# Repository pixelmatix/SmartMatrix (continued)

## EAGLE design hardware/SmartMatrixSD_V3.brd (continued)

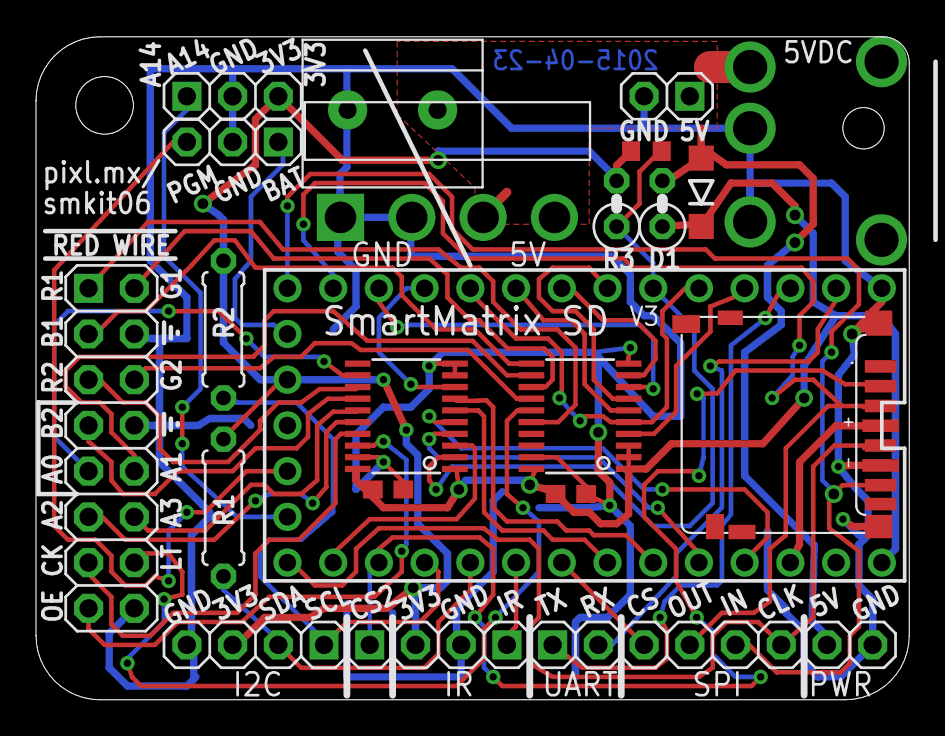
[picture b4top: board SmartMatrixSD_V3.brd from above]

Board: 2 copper layers, 48.5 x 36.8 mm, 25 parts (1 on the bottom side), 43 nets.

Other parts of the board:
U$5: PIXELMATIX-LOGO-235X135

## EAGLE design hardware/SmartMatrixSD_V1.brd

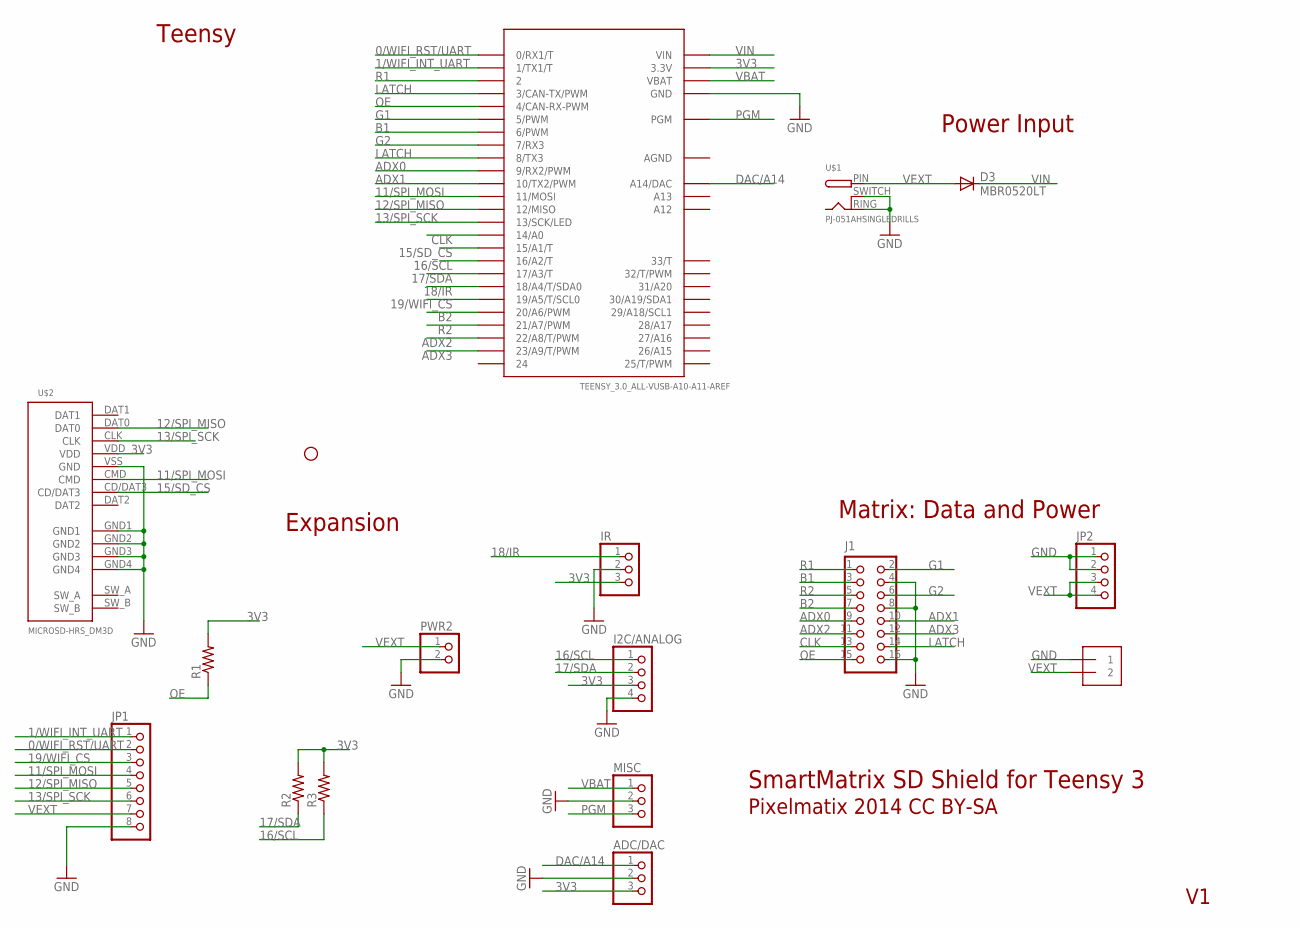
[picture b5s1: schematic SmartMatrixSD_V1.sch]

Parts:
ADC/DAC: PINHD-1X03_2.54-S; 1X03-S
D3: MBR0520LT; SOD123
I2C/ANALOG: PINHD-1X04_2.54-S; 1X04-S
IR: PINHD-1X03_2.54-S; 1X03-S
J1: CON_HEADER_2X08-PTH-SHROUDED; PINSHRD_PTH_2X08
J4: 1X2-5.0; 1X2-5.0MM
JP1: PINHD-1X08_2.54-S; 1X08-S
JP2: PINHD-1X04_1.56; 1X04-1.56"
JP5: STAND-OFFSTAND-OFF-3MM; STAND-OFF-3MM
MISC: PINHD-1X03_2.54-S; 1X03-S
PWR2: PINHD-1X02_2.54-S; 1X02-S
R1: R-US_R0603; R0603
R2, R3: R-US_0207/7; 0207/7
U$1: PJ-051AHSINGLEDRILLS; PJ-051AH-SINGLEDRILLS
U$2: MICROSD-HRS_DM3D; DM3D
U$3: TEENSY_3.0_ALL-VUSB-A10-A11-AREF; TEENSY_3.0_ALLPINS-VUSB-A11-A10-AREF

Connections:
0/WIFI_RST/UART: JP1.2, U$3.0 (0/RX1/T)
1/WIFI_INT_UART: JP1.1, U$3.1 (1/TX1/T)
3V3: ADC/DAC.3, I2C/ANALOG.3, IR.3, R1.2, R2.2, R3.2, U$2.VDD, U$3.3.3V, U$3.3.3V1 (3.3V), U$3.3.3V2 (3.3V)
11/SPI_MOSI: JP1.4, U$2.CMD, U$3.11 (11/MOSI)
12/SPI_MISO: JP1.5, U$2.DAT0, U$3.12 (12/MISO)
13/SPI_SCK: JP1.6, U$2.CLK, U$3.13 (13/SCK/LED)
15/SD_CS: U$2.CD/DAT3, U$3.15/A1 (15/A1/T)
16/SCL: I2C/ANALOG.1, R3.1, U$3.16/A2 (16/A2/T)
17/SDA: I2C/ANALOG.2, R2.1, U$3.17/A3 (17/A3/T)
18/IR: IR.1, U$3.18/A4 (18/A4/T/SDA0)
19/WIFI_CS: JP1.3, U$3.19/A5 (19/A5/T/SCL0)
ADX0: J1.9, U$3.9 (9/RX2/PWM)
ADX1: J1.10, U$3.10 (10/TX2/PWM)
ADX2: J1.11, U$3.22/A8 (22/A8/T/PWM)
ADX3: J1.12, U$3.23/A9 (23/A9/T/PWM)
AGND: U$3.AGND
B1: J1.3, U$3.6 (6/PWM)
B2: J1.7, U$3.20/A6 (20/A6/PWM)
CLK: J1.13, U$3.14/A0
DAC/A14: ADC/DAC.1, U$3.RESET (A14/DAC)
G1: J1.2, U$3.5 (5/PWM)
G2: J1.6, U$3.7 (7/RX3)
GND: ADC/DAC.2, I2C/ANALOG.4, IR.2, J1.4, J1.8, J1.16, J4.1, JP1.8, JP2.1, JP2.2, MISC.2, PWR2.2, U$1.RING (GND), U$1.SWITCH (GNDBREAK), U$2.GND1, U$2.GND2, U$2.GND3, U$2.GND4, U$2.VSS (GND), U$3.GND, U$3.GND1 (GND), U$3.GND2 (GND)
LATCH: J1.14, U$3.3 (3/CAN-TX/PWM), U$3.8 (8/TX3)
OE: J1.15, R1.1, U$3.4 (4/CAN-RX-PWM)
PGM: MISC.3, U$3.PGM
R1: J1.1, U$3.2
R2: J1.5, U$3.21/A7 (21/A7/PWM)
VBAT: MISC.1, U$3.VBAT
VEXT: D3.A, J4.2, JP1.7, JP2.3, JP2.4, PWR2.1, U$1.PIN (PWR)
VIN: D3.C, U$3.VIN

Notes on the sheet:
SmartMatrix SD Shield for Teensy 3
Pixelmatix 2014 CC BY-SA
Teensy
Power Input
Matrix: Data and Power
Expansion

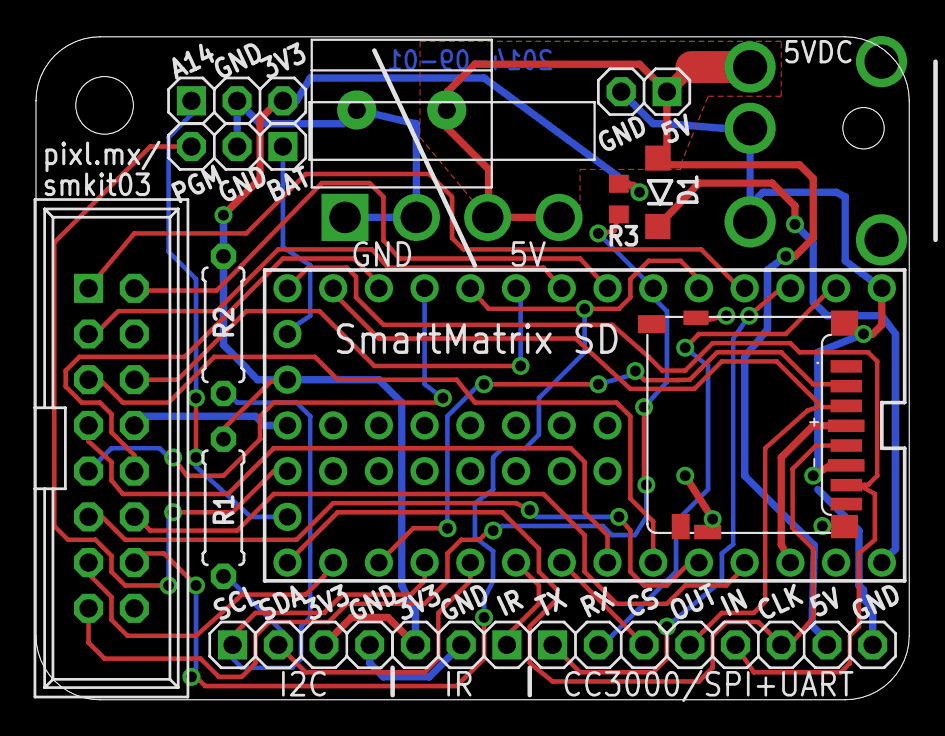
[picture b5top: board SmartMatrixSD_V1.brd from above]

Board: 2 copper layers, 48.5 x 36.8 mm, 17 parts (0 on the bottom side), 30 nets.

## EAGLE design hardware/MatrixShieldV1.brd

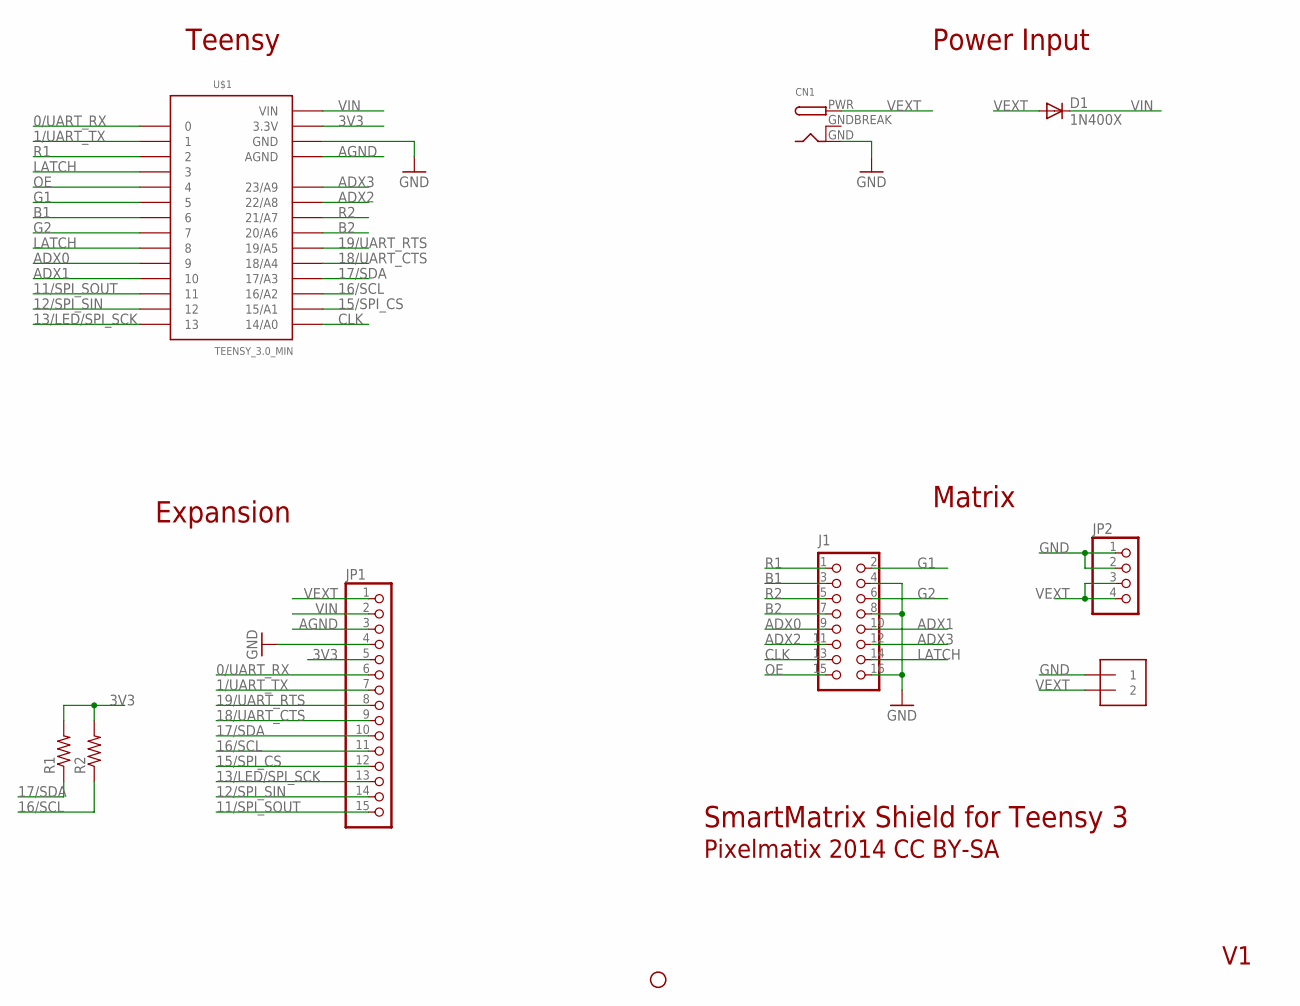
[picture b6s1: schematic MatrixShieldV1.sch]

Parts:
CN1: DCBARRELPTH; DCJACK_2MM_PTH
D1: 1N400X; DIODE-TH-0.3"
J1: CON_HEADER_2X08-PTH-SHROUDED; PINSHRD_PTH_2X08
J4: 1X2-5.0; 1X2-5.0MM
JP1: PINHD-1X15_2.54-S; 1X15-S
JP2: PINHD-1X04_1.56; 1X04-1.56"
JP5: STAND-OFFSTAND-OFF-3MM; STAND-OFF-3MM
R1, R2: R-US_0207/7; 0207/7
U$1: TEENSY_3.0_MIN

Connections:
0/UART_RX: JP1.6, U$1.0
1/UART_TX: JP1.7, U$1.1
3V3: JP1.5, R1.2, R2.2, U$1.3.3V
11/SPI_SOUT: JP1.15, U$1.11
12/SPI_SIN: JP1.14, U$1.12
13/LED/SPI_SCK: JP1.13, U$1.13
15/SPI_CS: JP1.12, U$1.15/A1
16/SCL: JP1.11, R2.1, U$1.16/A2
17/SDA: JP1.10, R1.1, U$1.17/A3
18/UART_CTS: JP1.9, U$1.18/A4
19/UART_RTS: JP1.8, U$1.19/A5
ADX0: J1.9, U$1.9
ADX1: J1.10, U$1.10
ADX2: J1.11, U$1.22/A8
ADX3: J1.12, U$1.23/A9
AGND: JP1.3, U$1.AGND
B1: J1.3, U$1.6
B2: J1.7, U$1.20/A6
CLK: J1.13, U$1.14/A0
G1: J1.2, U$1.5
G2: J1.6, U$1.7
GND: CN1.GND, J1.4, J1.8, J1.16, J4.1, JP1.4, JP2.1, JP2.2, U$1.GND
GNDBREAK: CN1.GNDBREAK
LATCH: J1.14, U$1.3, U$1.8
OE: J1.15, U$1.4
R1: J1.1, U$1.2
R2: J1.5, U$1.21/A7
VEXT: CN1.PWR, D1.A, J4.2, JP1.1, JP2.3, JP2.4
VIN: D1.C, JP1.2, U$1.VIN

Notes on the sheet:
SmartMatrix Shield for Teensy 3
Pixelmatix 2014 CC BY-SA
Teensy
Power Input
Matrix
Expansion

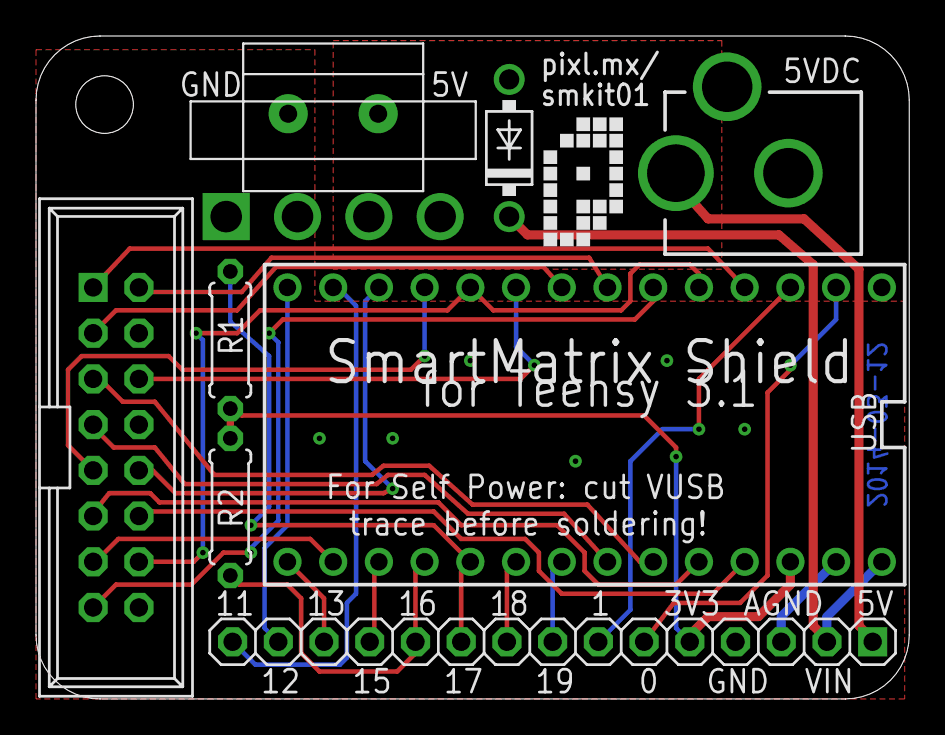
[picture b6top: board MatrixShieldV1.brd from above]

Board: 2 copper layers, 48.5 x 36.8 mm, 11 parts (0 on the bottom side), 28 nets.

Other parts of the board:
U$4: PIXELMATIX-LOGO-300

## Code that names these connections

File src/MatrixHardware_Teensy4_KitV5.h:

// Hardware-specific header file for the SmartLED Shield for Teensy 4 (V5):
//    Only Teensy 4.0/4.1 models are supported.
//
// Some of the pin assignments can be changed using solderable jumpers on the adapter board:
// JP4:
//    Default: Pin 7 connected to BUFFER_CLK, Pin 8 free
//    Alt: Pin 8 connected to BUFFER_CLK, Pin 7 free
//      To use the alternate clock pin, in addition to soldering the jumper you must set flag SMARTMATRIX_OPTIONS_T4_CLK_PIN_ALT in kMatrixOptions
// JP2 & JP3:
//    Default: Pin 4 connected to APA_CLK, Pin 5 connected to APA_DAT (intended for APA102 driving via SPI emulation), LED Matrix is drivable at the same time
//    Alt: Pins 4 & 5 free, Pin 13 connected to APA_CLK, Pin 11 connected to APA_DAT (intended for APA102 driving via hardware SPI), LED Matrix not drivable at the same time

// Note: only one MatrixHardware_*.h file should be included per project

#ifndef MATRIX_HARDWARE_H
#define MATRIX_HARDWARE_H

#pragma message "MatrixHardware: SmartLED Shield for Teensy 4 V1"

/* an advanced user may need to tweak these values */

// size of latch pulse - can be short for V4 shield which doesn't need to update ADDX lines during latch pulse
// 20 is minimum working value on DP5020B panel
// set to 100 for improved support with FM6126A panel
// don't exceed 150 to avoid interference between latch and data transfer
#define LATCH_TIMER_PULSE_WIDTH_NS 100

// max delay from rising edge of latch pulse to falling edge of first pixel clock
// increase this value if DMA use is delaying clock
// Measured 220 ns delay at 600 MHz clock speed, 160 ns at 816 MHz. Slower speeds are not supported.
// Using larger delay for safety.
#define LATCH_TO_CLK_DELAY_NS 400

// Pixel clock frequency is generated using the 480 MHz PLL3 clock and a divide-by-n counter. Frequency is independent of CPU clock speed.
// Must increment divider value by 2 (division ratio is always even)
// Minimum tested working value is 20 (corresponding to 24 MHz clock frequency) on DP5020B panel
// Using value of 26 (corresponding to 18.462 MHz clock frequency) to improve stability and reduce glitching
// Larger values may be more stable, but will decrease maximum refresh rate
#define FLEXIO_CLOCK_DIVIDER 26

// Amount of time required to transfer 32 pixels
// Adding 200 ns overhead time to improve stability
#define PANEL_32_PIXELDATA_TRANSFER_MAXIMUM_NS  ((32*FLEXIO_CLOCK_DIVIDER*1000/480) + 200)

/* this section describes how the microcontroller is attached to the display */

// these defines control the color channel assignments - if your panel has non-standard RGB order, swap signals here
#define R_0_SIGNAL    FLEXIO_PIN_R0_TEENSY_PIN
#define G_0_SIGNAL    FLEXIO_PIN_G0_TEENSY_PIN
#define B_0_SIGNAL    FLEXIO_PIN_B0_TEENSY_PIN
#define R_1_SIGNAL    FLEXIO_PIN_R1_TEENSY_PIN
#define G_1_SIGNAL    FLEXIO_PIN_G1_TEENSY_PIN
#define B_1_SIGNAL    FLEXIO_PIN_B1_TEENSY_PIN

//#define DEBUG_PINS_ENABLED
#define DEBUG_PIN_1 0
#define DEBUG_PIN_2 1
#define DEBUG_PIN_3 23

/************ The below definitions are unlikely to be useful if changed **************/

// active pin number definitions
// data bit order is calculated in setup using the pin number definitions and color channel assignments
// these pin definitions are also manually used to reset FM6126A panels
#define FLEXPWM_PIN_OE_TEENSY_PIN       2
#define FLEXPWM_PIN_LATCH_TEENSY_PIN    3
#define FLEXIO_PIN_CLK_TEENSY_PIN       7
#define FLEXIO_PIN_CLK_TEENSY_PIN_ALT   8
#define FLEXIO_PIN_B0_TEENSY_PIN        10
#define FLEXIO_PIN_R0_TEENSY_PIN        6
#define FLEXIO_PIN_R1_TEENSY_PIN        12
#define FLEXIO_PIN_G0_TEENSY_PIN        9
#define FLEXIO_PIN_G1_TEENSY_PIN        11
#define FLEXIO_PIN_B1_TEENSY_PIN        13

#define SMARTLED_APA_ENABLE_PIN         22
#define FLEXIO_PIN_APA102_CLK           4
#define FLEXIO_PIN_APA102_DAT           5

#define ADDX_0_SIGNAL   FLEXIO_PIN_R0_TEENSY_PIN
#define ADDX_1_SIGNAL   FLEXIO_PIN_G0_TEENSY_PIN
#define ADDX_2_SIGNAL   FLEXIO_PIN_B0_TEENSY_PIN
#define ADDX_3_SIGNAL   FLEXIO_PIN_R1_TEENSY_PIN
#define ADDX_4_SIGNAL   FLEXIO_PIN_G1_TEENSY_PIN

#else
    #pragma GCC error "Multiple MatrixHardware*.h files included"
#endif

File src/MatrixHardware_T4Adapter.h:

// Hardware-specific header file to use the SmartLED Shield V4 with the OSHPark Adapter for Teensy 4:
// https://oshpark.com/shared_projects/yVCGECuY
//    Only Teensy 4.0/4.1 models are supported.
//    Only SmartLED Shield V4 (for Teensy 3) is supported.
// No jumper wires or other modifications are needed with the OSHPark Adapter.
//
// Some of the pin assignments can be changed using solderable jumpers on the adapter board:
// JP1 & JP4:
//    Default: Pin 8 connected to BUFFER_CLK, Pin 7 free
//    Alt: Pin 7 connected to BUFFER_CLK, Pin 8 free
//      To use the alternate clock pin, in addition to soldering the jumpers you must set flag SMARTMATRIX_OPTIONS_T4_CLK_PIN_ALT in kMatrixOptions
// JP2 & JP3:
//    Default: Pin 4 connected to SPI_SCK, Pin 5 connected to SPI_MOSI (intended for APA102 driving via SPI emulation), LED Matrix is drivable at the same time
//    Alt: Pins 4 & 5 NC, Pin 13 connected to SPI_SCK, Pin 11 connected to SPI_MOSI (intended for APA102 driving via hardware SPI), LED Matrix not drivable at the same time
// The following unused Teensy 4 pins are made available on the shield but some are in different positions marked on the OSHPark Adapter:
//    Teensy 4 pins free:   0, 1, 7/8, 14, 15, 16, 17, 18, 19, 20, 21, 23
//    Locations on shield:  0, 1,   9, 10, 15, 16, 11, 18, 19, 12, 22, 23

// Note: only one MatrixHardware_*.h file should be included per project

#ifndef MATRIX_HARDWARE_H
#define MATRIX_HARDWARE_H

#pragma message "MatrixHardware: Teensy 4 Adapter attached to SmartLED Shield for Teensy 3 V4"

/* an advanced user may need to tweak these values */

// size of latch pulse - can be short for V4 shield which doesn't need to update ADDX lines during latch pulse
// 20 is minimum working value on DP5020B panel
// set to 100 for improved support with FM6126A panel
// don't exceed 150 to avoid interference between latch and data transfer
#define LATCH_TIMER_PULSE_WIDTH_NS 100

// max delay from rising edge of latch pulse to falling edge of first pixel clock
// increase this value if DMA use is delaying clock
// Measured 220 ns delay at 600 MHz clock speed, 160 ns at 816 MHz. Slower speeds are not supported.
// Using larger delay for safety.
#define LATCH_TO_CLK_DELAY_NS 400

// Pixel clock frequency is generated using the 480 MHz PLL3 clock and a divide-by-n counter. Frequency is independent of CPU clock speed.
// Must increment divider value by 2 (division ratio is always even)
// Minimum tested working value is 20 (corresponding to 24 MHz clock frequency) due to panel hardware limitations on the panels tested
// Using value of 24 (corresponding to 20 MHz clock frequency) because it seems to improve intermittent glitching issue
// Larger values may be more stable, but will decrease maximum refresh rate
#define FLEXIO_CLOCK_DIVIDER 24

// Amount of time required to transfer 32 pixels
// Adding 50 ns overhead time to improve stability
#define PANEL_32_PIXELDATA_TRANSFER_MAXIMUM_NS  ((32*FLEXIO_CLOCK_DIVIDER*1000/480) + 50)

/* this section describes how the microcontroller is attached to the display */

// these defines control the color channel assignments - if your panel has non-standard RGB order, swap signals here
#define R_0_SIGNAL    FLEXIO_PIN_R0_TEENSY_PIN
#define G_0_SIGNAL    FLEXIO_PIN_G0_TEENSY_PIN
#define B_0_SIGNAL    FLEXIO_PIN_B0_TEENSY_PIN
#define R_1_SIGNAL    FLEXIO_PIN_R1_TEENSY_PIN
#define G_1_SIGNAL    FLEXIO_PIN_G1_TEENSY_PIN
#define B_1_SIGNAL    FLEXIO_PIN_B1_TEENSY_PIN

//#define DEBUG_PINS_ENABLED
#define DEBUG_PIN_1 0
#define DEBUG_PIN_2 1
#define DEBUG_PIN_3 23

/************ The below definitions are unlikely to be useful if changed **************/

// active pin number definitions
// data bit order is calculated in setup using the pin number definitions and color channel assignments
// these pin definitions are also manually used to reset FM6126A panels
#define FLEXPWM_PIN_OE_TEENSY_PIN       2
#define FLEXPWM_PIN_LATCH_TEENSY_PIN    3
#define FLEXIO_PIN_CLK_TEENSY_PIN       8
#define FLEXIO_PIN_CLK_TEENSY_PIN_ALT   7
#define FLEXIO_PIN_B0_TEENSY_PIN        10
#define FLEXIO_PIN_R0_TEENSY_PIN        6
#define FLEXIO_PIN_R1_TEENSY_PIN        12
#define FLEXIO_PIN_G0_TEENSY_PIN        9
#define FLEXIO_PIN_G1_TEENSY_PIN        11
#define FLEXIO_PIN_B1_TEENSY_PIN        13

#define SMARTLED_APA_ENABLE_PIN         22
#define FLEXIO_PIN_APA102_CLK           4
#define FLEXIO_PIN_APA102_DAT           5

#define ADDX_0_SIGNAL   FLEXIO_PIN_R0_TEENSY_PIN
#define ADDX_1_SIGNAL   FLEXIO_PIN_G0_TEENSY_PIN
#define ADDX_2_SIGNAL   FLEXIO_PIN_B0_TEENSY_PIN
#define ADDX_3_SIGNAL   FLEXIO_PIN_R1_TEENSY_PIN
#define ADDX_4_SIGNAL   FLEXIO_PIN_G1_TEENSY_PIN

#else
    #pragma GCC error "Multiple MatrixHardware*.h files included"
#endif

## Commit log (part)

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2020-04-25 Fix README typo
2020-05-03 Previous commit broke backgroundLayer.swapBuffers(true) - fix
2020-05-05 Manually Merge #106 Add ESP32 wiring option for Wemos/Lolin chips
2020-05-08 README typo
2020-05-10 remove ESP32 Refresh dimming variables that were set but never used
2020-05-15 Handle PSRAM if available and enabled at compile time.
    Enabling PSRAM in the arduino GUI sets BOARD_HAS_PSRAM
    If it is defined, show PSRAM used/free along with rest of memory.
    Also fix heap_caps_get_free_size(MALLOC_CAP_INTERNAL) (using 0 was not
    correct).
    Allow allocating PSRAM for background buffers.
2020-05-15 Added ESP32-specific and niche application-specific code to scale (by bitwise shifting) Layer data to be brighter, and equally shifting matrix.brightness to be dimmer, to allow lesser significant bit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
2020-05-15 Remove unused variables
2020-05-15 Experimental FM6126A panel support, for ESP32 without external Latch - Related to #79 - make LAT pulse 3x clocks wide, matching the FM6126A "DATA_LATCH" command (and not the "RESET_OEN" command) - Te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
2020-05-17 Some notes on ESP32 hardware
2020-05-19 Fix backgroundLayer.enableColorCorrection() bug, doesn't work for COLOR_DEPTH 48
2020-05-20 Readme: Add a bit more detail to ESP32 Hardware section
2020-05-23 Add missing Layer.begin() calls to seldom-used MatrixCalc classes
2020-05-25 committed to wrong folder
2020-05-25 Teensy3 APA102 - Add option to use IntervalTimer instead of directly using FTM2 peripheral
2020-05-25 Teensy3 APA102 - Set priority of ISR back to normal
2020-05-25 Teensy 4 - add missing FLEXIO APA pins to MatrixHardware_KitV4T4.h
2020-05-30 Improved DMA usage of FlexIO driver
    Number of FlexIO shifters used for data buffering now configurable from 1 to 4; was hardcoded at 2 before.
2020-05-31 Change ESP32 HUB75 NT (no template) class to remove static methods, and load major parameters as consts with member initialization list
2020-05-31 Limit #includes to SmartMatrix3.h from .cpp files, which currently pull in default MatrixHardware* files - we want to remove dependence on default MatrixHardware files so hardware can be defined in S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
2020-06-02 Add new MatrixHardware for HUB75 Adapter THT
2020-06-02 Make ESP32 HUB75 _NT class static so allocate buffers can be used inside setup()
2020-06-08 Add T4 Kit header + custom color support
    Add new header for SmartLED Shield for Teensy 4 V0
    Update Teensy 4 headers to use color channel assignment #defines (in line with NT branch)
    Update .cpp file #includes to remove dependence on default MatrixHardware files (copying NT branch)
    Remove kMatrixOptions flags for custom RGB - user can now configure this in custom hardware header.
2020-06-11 ESP32 HUB75 Calc - Only calc new frame if any of the layers need it
2020-06-13 ESP32 HUB75_NT - only load user-settable parameter defaults if they haven't already been set before begin() was called
2020-06-14 Modify FeatureDemo to use custom hardware header
2020-06-15 fix blank screen
    fixed issue where screen would crash in startup if default refresh rate (120) was higher than allowed maximum
2020-06-18 Reverse Allow for fast BackgroundLayer buffer swaps on platforms that support it (ESP32) ce1e89
2020-06-20 Bitmaps Example - Allow disabling LED flash as it now interferes with Teensy 4
2020-06-22 move cache flush before cbWrite
    avoid potential issue where next row is displayed before cache is flushed
2020-06-26 Update MatrixHardware_Teensy4_KitV0.h
    update default timing constants
2020-06-26 Update FastLED_Functions.ino
    delete unused header
2020-06-26 Update MultipleTextLayers.ino
    remove unused header
2020-06-26 Update MatrixClock.ino
    remove unused header
2020-07-06 Remove duplicate #includes
2020-07-26 Place font bitmaps into flash on T4
    Teensy 4.x uses PROGMEM to put arrays into flash instead of RAM (unlike T3.x where just declaring const was enough)
2020-08-20 Add SmartLED Shield for Teensy 4 Hardware Files
2020-08-21 README
2020-09-05 Update Layer_Indexed to use swapBuffers like Layer_Background
2020-09-06 Rearrange BackgroundGFX methods
2020-09-07 Add uint16_t to rgb16/rgb24 conversions to simplify Adafruit_GFX drawPixel(uint16_t) wrapper function
2020-09-07 Explicitly set rotationDegrees values for Adafruit_GFX compatibility
2020-09-07 Layer_BackgroundGFX - Add backwards compatible support for drawing fonts and chars using Adafruit_GFX library (limited to one font option for now), and drawString with background isn't supported yet
2020-09-08 Remove leftover function definition
2020-09-08 Layer_BackgroundGFX - rename x/yOffset to unique name
2020-09-09 Layer_BackgroundGFX - For consistency if not for more important reasons, use "this->" for all references to matrixWidth/Height
2020-09-12 Layer - move getRotation inside Layer class, make setRotation virtual
2020-09-12 Layer_BackgroundGFX - Update ESP32 macro (untested)
2020-09-12 Featuredemo - Complete list of Built In Fonts
2020-09-12 Layer_BackgroundGFX - Move old variable into old code section
2020-09-13 Layer_GFX_Mono: Add helper function some Adafruit_GFX sketches rely on
2020-09-13 Update MultipleTextLayersGFX demo to use new GFX_Mono Layer, Adafruit_GFX fonts, randomized parameters
2020-09-13 MultipleTextLayers example - add refresh rate print to loop
2020-09-13 Layer_GFX_Mono - Add ALLOCATE macros
2020-09-13 FastLED_Functions Example - add explicit cast from CRGB to rgb24. With new uint16_t conversions for Adafruit_GFX, the compiler gets confused as to which type we want
2020-09-14 MultipleTextLayersGFX Example - simplify CRGB to rgb24 conversion
2020-10-11 Add MatrixHardware_Teensy4_KitV5.h, describing production version of SmartLED Shield for Teensy 4
2020-10-11 Add credits for FlexIO_t4
2020-10-11 Teensy 3 48-bit refresh - Fix reversed logic for SMARTMATRIX_OPTIONS_BOTTOM_TO_TOP_STACKING with Z-shaped stacking, and make clearer comment on data order (this is broken and needs to be fixed for ot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
2020-10-12 Teensy 4: add SMARTMATRIX_OPTIONS_C_SHAPE_STACKING functionality for normal panels - Fix reversed logic for SMARTMATRIX_OPTIONS_BOTTOM_TO_TOP_STACKING with Z-shaped stacking, and make clearer comment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
2020-10-13 Teensy 4 HUB75 - added MULTI_ROW_REFRESH_REQUIRED precompiler which works for normal panels but not for MULTI_ROW_REFRESH_REQUIRED = true
2020-10-13 Teensy 3 HUB75 - refactor loadMatrixBuffers() based on improved Teensy 4 version - set all color bits at a time for each pixel, which seems to be over 10% more efficient for normal panels - use a sin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
2020-10-13 Remove references to MCPWM peripheral, which we no longer use
2020-10-18 ESP32 HUB75 NT: Fix frameStruct malloc call so it allocates the correct amount of ram for sizeof(MATRIX_DATA_STORAGE_TYPE) > 1
2020-10-18 ESP32 HUB75 NT - clean up types used for class parameters
2020-10-19 ESP32 HUB75 NT - match debug printfs to normal ESP32 HUB75 class
2020-11-03 Set FeatureDemo default refresh depth back to 36
2020-11-03 Reorganizing Files - Remove obsolete Coprocessor classes
2020-11-03 Rename MatrixHardware files to be more clear, update headers in sketches
2020-11-03 Reorganizing Files - Add "Common" for platform type for APA classes
2020-11-05 APA102 Teensy 3 - add missing #include
2020-11-08 Fix setBrightness(0) bug
    off-by-one error in Teensy 4 PWM registers caused setBrightness(0) to not turn off the display completely
2020-11-19 APA102 - add note on serpentine data layout
2020-11-20 APA102 - add RGB/BGR/etc color order options
2020-11-21 Rename SmartMatrix* files to Matrix*
2020-11-23 HUB75 - Rename paneltype definitions from SMARTMATRIX_HUB75_* to SM_PANELTYPE_HUB75_*
2020-11-23 Remove no longer relevant example
2020-11-24 Update/add copyright message to source files
2020-11-24 Rename *HUB75* and *ESP32* files to *Hub75* and *Esp32*, skipping MatrixHardware*.h
2020-11-24 Rename SmartMatrix3.h to SmartMatrix.h, add SmartMatrix4.h - keep "SmartMatrix3_h" definition, and purposely don't define "SmartMatrix_h" for FastLED compatibility - Add unique "SmartMatrix4.h" in ca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
2020-11-24 Update Copyright to 2020
2020-11-25 Add SmartMatrix Library 4.0 details to MIGRATION document
2020-11-25 Add version number pragma/warning/define copied from FastLED
2020-11-25 Add unmodified FlexIO_t4 library to repository - Oct 6, 2020 e764ed7b0d84faca05a18b5e3d739a7b52551372 commit
2020-11-26 Move photos to GitHub Pages
2020-11-26 MatrixHardware - fix wrong rev number, and make revisions more clear
2020-11-29 Update MIGRATION
2020-11-30 esp32 - comment out unused functions from Espressif code
2020-11-30 MatrixHardware - add already used GPIOPINOUT defines
2020-11-30 Layer_Gfx_Mono - clear full buffer, which may be larger than matrixWidth*matrixHeight*2
2020-11-30 update keywords for next release
2020-12-01 Examples - Remove accidentally uncommented MatrixHardware files
2020-12-08 Esp32Hub75_NT - rearrange const arguments set in constructor to avoid compiler warnings
2020-12-11 APA102 Example - remove accidentally committed test code
2020-12-12 APA102 Controller - Add bounds checking on pixelIndex
2020-12-12 APA102 Example - add apamatrix.countFPS() if (ENABLE_HUB75_REFRESH == 0)
2020-12-21 MultipleTextLayersGfx Example - Fix issue with old GFX defines used with INCLUDE_FASTLED_BACKGROUND option
2020-12-29 Fix SmartMatrix Community links
2021-01-01 updated FastLED conversion
2021-01-03 HUB12 testing - add options for selective inversion of OE and data signals
2021-01-09 SpectrumAnalyzer_I2s example - add Teensy 3 pinout and missing header file
2021-01-24 fix(fillnoise8): remove seams on non-square matrices
2021-03-09 Add MatrixHardware_ESP32_SmartLedShieldV0.h
2021-06-09 add default pin assignment as it was found in mrfaptastic/ESP32-HUB75-MatrixPanel-I2S-DMA
2021-07-20 Applied patch from https://community.pixelmatix.com/t/mapping-assistance-32x16-p10/889/23 not fully integrated (added Teensy 4 code for testing)
2021-11-19 Add SM_PANELTYPE_HUB75_16ROW_32COL_MOD2SCAN_V2 support for Teensy 3/4, ready for testing - Added PANEL_USES_ALT_ADDRESSING_MODE as there is more than one panel type using this new method
2021-12-17 Layer private members made protected
2021-12-18 Option to disable versioning messages
2022-08-07 Update README.md
    Correcting renamed wiki page.
2023-10-25 Update esp32_i2s_parallel.c
    Update includes to support platform 2.0.x
2023-11-26 Refactor I2S setup in MatrixEsp32Hub75Refresh_Impl.h and MatrixEsp32Hub75Refresh_NT_Impl.h
    - Refactored the I2S setup code in both files to use named parameters for better readability and maintainability.
    - Replaced direct assignments with named parameter assignments for desccount_a, desccount_b, lldesc_a, and lldesc_b.
2024-01-10 gitflow-feature-stash: ELECTRODRAGON_PINOUT
2024-01-10 Update pin assignments for demux inputs A0 and A1 in MatrixHardware_ESP32_V0.h
    The pin assignments for demux inputs A0 and A1 have been updated from GPIO_NUM_5 and GPIO_NUM_18 to GPIO_NUM_19 and GPIO_NUM_21 respectively. This change ensures correct functionality of the code.
